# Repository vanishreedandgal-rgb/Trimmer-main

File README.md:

# Trimmer-main
You can use this 2-line description:  KiCad schematic and PCB design for a Trimmer project.Includes circuit schematic, PCB layout, and design files.

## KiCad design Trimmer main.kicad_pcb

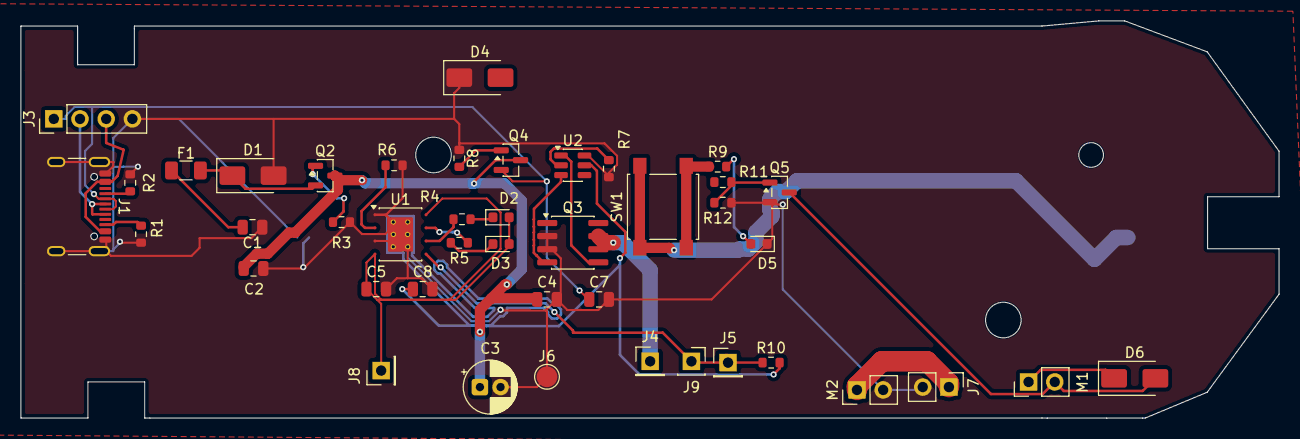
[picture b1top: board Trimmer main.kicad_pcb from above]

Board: 2 copper layers, 122.0 x 38.5 mm, 44 parts (1 on the bottom side), 30 nets.

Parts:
BT1: Battery_Cell; BatteryHolder_Keystone_1042_1x18650
C1, C2, C5: 10uF; C_0805_2012Metric
C3: 10uF; CP_Radial_D5.0mm_P2.00mm
C4, C8: 100nF; C_0805_2012Metric
C7: 10uf; C_0805_2012Metric
D1: SMAJ9.0A; D_SMA
D2, D3, D5: LED; LED_0603_1608Metric
D4: SS14; D_SMA
D6: D_Schottky; D_SMA
F1: 2A; Fuse_1206_3216Metric
J1: HC-TYPE-C-16P-01A; USB_C_Receptacle_GCT_USB4105-xx-A_16P_TopMnt_Horizontal
J3: Conn_01x04_Pin; PinHeader_1x04_P2.54mm_Vertical
J4: BAT-; PinHeader_1x01_P2.54mm_Vertical
J5: BAT+; PinHeader_1x01_P2.54mm_Vertical
J6: GND; TestPoint_Pad_D2.0mm
J7: Conn_01x02_Pin; PinHeader_1x02_P2.54mm_Vertical
J8: VIN 5V; PinHeader_1x01_P2.54mm_Vertical
J9: Conn_01x01_Socket; PinSocket_1x01_P2.54mm_Vertical
M1, M2: Motor_DC; PinHeader_1x02_P2.54mm_Vertical
Q2, Q4: AO3401A; SOT-23
Q3: FS8205A; SOIC-8_3.9x4.9mm_P1.27mm
Q5: Q_NMOS_GSD; SOT-23
R1: 5.1kohm; R_0603_1608Metric
R2: 5.1k0hm; R_0603_1608Metric
R3: 100kohm; R_0603_1608Metric
R4, R5: 1kohm; R_0603_1608Metric
R6: 1KOHM; R_0603_1608Metric
R7, R9: R; R_0603_1608Metric
R8: 100KOHM; R_0603_1608Metric
R10, R11: 100ohm; R_0603_1608Metric
R12: 10kohm; R_0603_1608Metric
SW1: SW_SPST; SW_SPST_B3S-1000
U1: TP4056-42-ESOP8; SOIC-8-1EP_CUSTOM
U2: DW01A; SOT-23-6

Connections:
+5V: C2.1, C3.1, C4.1, Q2.3 (D), Q4.3 (D)
CHRG: R4.2, U1.6 (~STDBY)
GND: BT1.2 (-), C1.2, C2.2, C3.2, C4.2, C5.2, C7.2, C8.2, D1.2 (A2), D4.1 (K), D5.1 (K), J1.A1 (GND), J1.A12 (GND), J1.B1 (GND), J1.B12 (GND), J1.SH (SHIELD), J3.4, J6.1 (Pin_1_1), J7.2, M2.2 (-), Q3.2, Q3.3, Q5.2 (S), R1.2, R2.2, R3.2, R6.2, R7.2, R8.2, R12.2, U1.1 (TEMP), U1.3 (GND), U1.9 (EPAD), U2.6 (GND)
unnamed: BT1.1 (+), SW1.1 (A)
unnamed: C1.1, F1.1
unnamed: D1.1 (A1), F1.2, Q2.2 (S)
unnamed: D2.1 (K), R4.1
unnamed: D3.1 (K), R5.1
unnamed: D5.2 (A), R9.2
unnamed: D6.2 (A), M1.2 (-), Q5.3 (D)
unnamed: D6.1 (K), M1.1 (+)
unnamed: J1.A5 (CC1), R2.1
unnamed: J1.B5 (CC2), R1.1
unnamed: J1.A6 (D+), J1.B6 (D+), J3.2
unnamed: J1.A4 (VBUS), J1.A9 (VBUS), J1.B4 (VBUS), J1.B9 (VBUS), J3.3
unnamed: J4.1 (Pin_1_1), Q3.6, Q3.7
unnamed: J5.1 (Pin_1_1), J9.1 (Pin_1_1), R10.1, U1.5 (BAT)
unnamed: J7.1, M2.1 (+)
unnamed: Q2.1 (G), R3.1
unnamed: Q4.1 (G), R8.1
unnamed: Q5.1 (G), R11.2, R12.1
unnamed: R6.1, U1.2 (PROG)
unnamed: R7.1, U2.2 (CS)
unnamed: Q3.4, U2.3 (OC)
unnamed: Q3.5, U2.1 (OD)
unnamed: C8.1, R10.2, U2.5 (VCC)
STDB: R5.2, U1.7 (~CHRG)
VBUS_5V(INPUT 5V): C5.1, D2.2 (A), D3.2 (A), J8.1 (Pin_1_1), U1.4 (V_{CC}), U1.8 (CE)
VCC: R9.1, SW1.2 (B)
VUSB_5V: C7.1, J1.A7 (D-), J1.B7 (D-), J3.1, Q4.2 (S)
